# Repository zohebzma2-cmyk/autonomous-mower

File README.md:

# Autonomous Zero-Turn Retrofit Kit

> **Most open-source mowers convert a toy robot-mower. This retrofits a 615 lb commercial gas zero-turn.**

*Parametric CAD, spec-matched to the full published envelope (1968 × 1610 × 1039 mm · deck 1321 mm · tyres 508/279 mm) — [still renders](gallery.html) · [carrier PCB](hardware/pcb/)*

Turn a seated zero-turn mower into a self-driving, iPad-controlled robot — **RTK GPS + LiDAR + cameras + on-device AI** — weatherproofed to live outdoors, and **reproducible on any ZTR** by re-measuring a handful of dimensions.

> **Status: 🔧 in active build.** Design, CAD, firmware, control software, and docs are complete and verified (69/69 tests). The machine is currently being built in person — parts on order, brackets printing, wiring the kill-chain first. This is a multi-month, safety-gated build, documented as it happens — not a plug-and-play kit.

**Confirmed reference machine:** Gravely **ZT X 52** · ~2021 · **Kohler 7000** (24 hp, 725 cc) · electric PTO clutch.

> 🏁 **New here? Start with [`docs/00-BUILD-MANUAL.md`](docs/00-BUILD-MANUAL.md)** — the end-to-end build sequence.
>
> 🕹️ **Already RC-controlled (tracked / slope mower)?** [`docs/ADAPT-RC-MOWER.md`](docs/ADAPT-RC-MOWER.md). The Pixhawk drops in front of the stock drive controller, so you skip the actuators and ESP32.
>
> 🚜 **Phase 3 — the whole rig:** [`docs/ATTACHMENTS.md`](docs/ATTACHMENTS.md) — self-dumping power bagger, rotating blower/trimmer boom, FIMCO tow sprayer with speed-proportional dosing, TPMS, self-start ignition + choke, and the no-rut 3-point turn planner (physics inside).
>
> 📓 **How it evolved:** [`docs/DESIGN-LOG.md`](docs/DESIGN-LOG.md) — every iteration, every wrong turn, constraints A–Z.
> **What's next:** [`docs/ROADMAP-75.md`](docs/ROADMAP-75.md) — 75 planned upgrades.
> **Ordering:** [`cart/ORDER.md`](cart/ORDER.md) + machine-readable [`cart/ORDER-SHEET.csv`](cart/ORDER-SHEET.csv).
> **Building:** [`docs/MEASURE.md`](docs/MEASURE.md) (the 10-minute caliper session — do this first) · [`docs/PRINT-QUEUE.md`](docs/PRINT-QUEUE.md) (40 parts, grams + hours) · [`docs/TOOLS.md`](docs/TOOLS.md) · [`docs/SUBSTITUTIONS.md`](docs/SUBSTITUTIONS.md) · [`docs/CHANGELOG.md`](docs/CHANGELOG.md).
>
> 🌐 **Interactive writeup:** [zohebalvi.com/projects/autonomous-mower](https://zohebalvi.com/projects/autonomous-mower.html) — 3D model, live control-UI demo, architecture, and the full parts list with order links.

> ⚠️ **A 52″ mower deck can kill.** Read [`docs/BUILD.md` §0 Safety](docs/BUILD.md) before powering anything. **Blades stay disconnected until drive + navigation + every failsafe is proven.**

---

## The architecture in one line

**ArduPilot Rover** on a Pixhawk 6C owns drive + RTK navigation + the failsafe chain (skid-steer fits a ZTR natively); a **Raspberry Pi 5 + Hailo-8L** (13 TOPS) rides shotgun for LiDAR obstacle-stop and camera AI, talking to the FC over MAVLink; an **ESP32** closes the lap-bar position loop the autopilot can't drive directly. One web UI serves both an iPad over WiFi and an on-unit touchscreen.

```
        ┌───────────── SENSE ─────────────┐   ┌────── THINK ──────┐   ┌──── ACT ────┐
  Dual RTK GPS (±2 cm, ~0.4° heading) ─────┼──► Pixhawk 6C ────────┼──► lap-bar L/R
  360° LiDAR ──────────────┐               │   (ArduPilot Rover)   │   (via ESP32)
  Front + rear cameras ────┼──► Pi 5 + Hailo├── MAVLink ───────────┤
  Overhead ultrasonic ─────┘   (vision/UI) │   ESP32 (lap-bar PID) ├──► PTO relay
                                           └───────────────────────┘   (blades)
```

---

## The machine — down to the millimetre

| | Gravely ZT X 52 (Kohler 915256) |
|---|---|
| Overall | **1968 × 1610 × 1039 mm** (L×W×H) |
| Curb weight | 615 lb (279 kg) |
| Cutting deck | **1321 mm** (52″), 11-ga fabricated |
| Rear drive wheels | 20×10-8 → **Ø 508 mm**, 254 mm wide |
| Front casters | 11×6-5 → **Ø 279 mm** |
| Seat pan height | 580 mm off ground (**no factory ROPS**) |
| Frame rail | 50.8 mm square tube |
| Lap-bar tube | **Ø 25.4 mm** round steel (MIC to confirm), 560 mm spacing, ~90 mm throw |
| Powertrain | 24 hp Kohler 7000 (725 cc) · Hydro-Gear ZT-2200 · 7 mph · **electric PTO** |

Retrofit parts are modeled to their datasheets — e.g. the **PA-14P actuator** (retracted 241.6 mm, Ø38.1 mm body, 6.35 mm clevis pin), **simpleRTK2B** (68.58 × 53.34 mm, Arduino-Uno footprint), **RPLidar A1M8** (teardrop 96.74 × 70.28 mm base). See [`cad/params.scad`](cad/params.scad).

---

## What's in the repo

```
autonomous-mower/
├── docs/
│   ├── 00-BUILD-MANUAL.md   ← START HERE — Phase 0–6 build sequence
│   ├── BUILD.md             ← full build & SAFETY spec (architecture, training, go/no-go)
│   ├── WIRING.md            ← power distribution, kill-chain, per-module pinouts
│   ├── PRINT_GUIDE.md       ← per-part orientation, brim, supports, plate batching
│   └── wiring-diagram.svg
├── cad/                     ← parametric OpenSCAD — 40 print-ready parts
│   ├── params.scad          ← ★ MASTER PARAMETERS — edit SECTION 1 to fit any ZTR
│   ├── assembly.scad        ← whole machine; SHOW=all|body|black|retro for multi-material export
│   ├── mower.scad           ← parametric mower mock (context)
│   ├── {enclosure,actuator_brackets,gps_mast,lidar_mount,camera_mount,controls_bracket,badge,attachments_brackets,sensor_mounts}.scad
│   ├── export_stl.sh        ← export every PRINT_* part + bed-fit gate (rejects > 145 mm)
│   ├── bake_brims.sh        ← welds a bed-adhesion brim onto every part
│   ├── render_gallery.sh · render_hero.py ← gallery stills · README orbit GIF + social card
│   └── stl/ · renders/ · vendor/
├── software/
│   ├── companion/           ← Python: app.py (HTTP+SSE), safety.py, vision.py, missions.py, mav.py
│   ├── ui/                  ← the control UI (iPad + on-unit kiosk)
│   ├── tests/               ← 69 stdlib tests (safety, geofence, attachments, turns, coverage, keep-outs, vision, mission encoding)
│   └── deploy/              ← systemd service + Chromium kiosk autostart
├── firmware/
│   ├── lapbar_controller/   ← ESP32: FC-PWM → pot → BTS7960 position loop, fail-to-neutral
│   └── ardupilot/           ← rover_params.parm (skid-steer, RTK, geofence, moving-baseline)
├── hardware/pcb/            ← ★ MowerCarrier: power + kill-chain + ESP32 carrier board
│   └── kicad/               ← generated KiCad 9 project (ERC/DRC clean) + Gerbers — read REVIEW.md before fab
│   ├── schematic.svg · layout.svg · render-*.png   ← exported from the KiCad project
│   └── README.md · netlist.md · BOM.md · FABRICATION.md
└── cart/                    ← ORDER.md (real BOM + links), order.html
```

---

## Quickstart

### CAD → STL
```bash
cd cad
# 1. Edit params.scad SECTION 1 to your machine — start from a profile in cad/profiles/
#    (zt-x-52.scad = the reference build; generic-60in.scad = commercial-class starting point)
#    or generate your block interactively: zohebalvi.com/mower → "Adapt it to YOUR mower"
openscad assembly.scad          # see the whole machine
./export_stl.sh                 # export all printable parts + bed-fit check
./bake_brims.sh                 # weld brims for adhesion
./render_gallery.sh             # machine stills; python3 render_hero.py re-shoots the orbit GIF (needs Pillow)
# slice cad/stl/brim/*.stl in FlashPrint for the Adventurer 3 (ASA or PETG)
```

### Dev setup (once — user-level, no sudo/Homebrew)
```bash
./scripts/setup-dev.sh            # uv + Python 3.12 .venv + OpenSCAD (+ --kicad: KiCad, Freerouting, arduino-cli)
./scripts/check.sh --full --sitl  # every gate: tests, mypy, CAD asserts, renders, docs, SITL end-to-end
```

### Control software (runs today, no hardware)
```bash
python3 software/companion/app.py --sim --port 8080
# open http://localhost:8080 — arm, draw a zone, run a coverage mission in simulation
python3 software/tests/test_backend.py       # 69/69
./scripts/sitl.sh                 # the REAL ArduPilot Rover 4.7.1 firmware (SITL) behind the same UI
```

### Firmware
- **ESP32:** flash `firmware/lapbar_controller/lapbar_controller.ino` (Arduino IDE / arduino-cli).
- **ArduPilot:** load `firmware/ardupilot/rover_params.parm` in Mission Planner (skid-steer + RTK + failsafes; moving-baseline block commented for the dual-antenna heading upgrade).

---

## Training — all three, built in order

1. **Teach-and-repeat** — drive the path once, it repeats the RTK track.
2. **Boundary → auto-coverage** — drive the perimeter, the planner fills it with rows and uploads them as an ArduPilot AUTO mission. It handles real yards: L/U shapes (cell decomposition, routed transits), rows along the direction with the fewest turns, **keep-outs** (beds, trees, the shed — or spots the sonar keeps hitting), no-rut turns with **perimeter laps** for the headland, and shows m², minutes and % covered before it moves.

3. **AI learns the yard** — the camera/LiDAR model refines a semantic map over runs (Hailo).

---

## Precision

The upgrade that matters is **dual-antenna moving-baseline heading**. One RTK antenna gives a great position but a noisy heading at a standstill; a second antenna on a ≥ 500 mm baseline fixes heading geometrically (~0.4°), turning ~10 cm cross-track into a few cm. Config in `firmware/ardupilot/rover_params.parm`.

| | |
|---|---|
| Position | **±2 cm** RTK-fixed (u-blox ZED-F9P) |
| Heading | **~0.4°** moving-baseline (dual antenna) |
| Cross-track | few cm, row to row |
| On-device AI | **13 TOPS** (Hailo-8L), INT8, < 30 ms target, no cloud (model training is hardware-gated) |

---

## Safety — a layered kill chain (wire & test this FIRST)

No single failure leaves the machine moving. Blades stay disconnected until every layer is proven.

1. **Physical e-stop** (normally-closed) — in series with the drive relay + PTO relay; cuts power independent of any code.
2. **RC kill** — an independent FlySky channel → ArduPilot RC failsafe → HOLD + disarm.
3. **Software interlock** (`safety.py`) — evaluates incline (15° cutoff), overhead (1.6 m), and obstacle every cycle; priority `e-stop > slope > overhead > obstacle`.
4. **Fail-to-neutral** — on e-stop or signal loss the ESP32 drives the lap bars to center, then coasts; ArduPilot failsafes (GPS loss, geofence, low battery) hold.

Full pinout + kill-chain wiring in [`docs/WIRING.md`](docs/WIRING.md).

---

## Bill of materials

Real, in-stock parts — verified against live listings, no fabricated SKUs. Two tiers: **functional ≈ $1,644**, or **precision ≈ $1,812** with the dual-antenna heading kit. Full itemized sheet with links in [`cart/ORDER.md`](cart/ORDER.md).

- **Navigation / compute:** Pixhawk 6C ([Holybro](https://holybro.com/products/pixhawk-6c)) · simpleRTK2B + ANN-MB-00 ([ArduSimple](https://www.ardusimple.com/product/simplertk2b/)) · Pi 5 + Hailo AI HAT+ ([PiShop](https://www.pishop.us/product/raspberry-pi-ai-hat-13-tops/))
- **Perception:** RPLidar A1M8 · 2× Pi Camera 3 · JSN-SR04T ultrasonic
- **Steering / drive:** 2× Progressive Automations PA-14P · 2× BTS7960 · ESP32
- **Safety / power:** IP65 NC e-stop · 40 A relays · PM02 power module · fuse block · bucks

---

## Adapting to another zero-turn

Open [`cad/params.scad`](cad/params.scad) → **SECTION 1**, re-measure the lap bars / frame / seat, re-render, re-slice. That's the whole port — the mounts, brackets, and masts regenerate around your numbers. Toro, Bad Boy, Spartan, Ferris, Scag, etc.

---

## Status & honest limitations

Design + CAD + firmware + control software + docs are complete and verified (69/69 tests). The build is **in progress in person**. Remaining work is hardware-gated: SITL/on-FC validation of the MAVLink handshake, training the Hailo `.hef` model, and the future fleet/RaaS layer. See [`docs/BUILD.md §12`](docs/BUILD.md).

## Related open-source mowers & rovers

This project stands on the shoulders of a great open community — go star these too:

- **[OpenMower](https://github.com/ClemensElflein/OpenMower)** (Clemens Elflein) — the flagship: retrofits *consumer* robot mowers with a custom mainboard + RTK + ROS. Same RTK/Pi/vision philosophy; we take it to a full-size gas ZTR.
- **[Ardumower / Sunray](https://github.com/Ardumower/Sunray)** — the original DIY-mower ecosystem; Sunray pioneered RTK-without-a-perimeter-wire.
- **[ArduPilot Rover](https://ardupilot.org/rover)** — the autopilot this build runs. The [robot-mower threads](https://discuss.ardupilot.org/t/robot-mower-based-on-ardurover/61999) on their Discourse are the best place to talk shop.
- **[Twisted Fields — Acorn](https://github.com/Twisted-Fields/acorn-precision-farming-rover)** & **[FarmBot](https://github.com/farmbot)** — adjacent open outdoor-autonomy / ag-robotics done well.

## Community & contributing

- 💬 **[GitHub Discussions](https://github.com/zohebzma2-cmyk/autonomous-mower/discussions)** — *Show & Tell* your ZTR build, ask in *Q&A*, propose *Ideas*, follow *Build logs*.
- 🔧 **Adapting to a different zero-turn?** That's the whole point — a new machine profile is the most valuable contribution you can make. See [`Adapting to another zero-turn`](#adapting-to-another-zero-turn) and open a PR with your `params.scad` SECTION 1.
- 🛠️ **Custom carrier PCB** — the power/kill-chain/ESP32 board lives in [`hardware/pcb/`](hardware/pcb/): a routed, ERC/DRC-clean KiCad 9 project generated from one Python file, with Gerbers ready for review ([`REVIEW.md`](hardware/pcb/kicad/REVIEW.md) first). Remix it for your machine.
- See [`CONTRIBUTING.md`](CONTRIBUTING.md) for the safety-gated workflow. Good first issues are labeled `good first issue`.

## License & safety

Open source under the [MIT License](LICENSE). ⚠️ **This drives a machine with large blades that can kill** — it's released for education/research; you are solely responsible for safe construction, testing, supervision, and local-law compliance. Keep blades disconnected until every failsafe is proven.

*A personal robotics project by [Zoheb Alvi](https://zohebalvi.com).*

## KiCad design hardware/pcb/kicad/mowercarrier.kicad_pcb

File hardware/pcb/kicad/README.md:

# MowerCarrier Rev A.1 — KiCad 9 project (generated)

Power input + reverse-polarity protection + 30 A main fuse + five fused branches, the
hardware kill chain (E-stop NC contacts in series with FET-switched relay coils), and the
ESP32-DevKitC carrier for the lap-bar controller. 120 × 100 mm, 2 layers, 2 oz copper.

**The `.kicad_*` files are generated. Edit `design.py` (parts + nets) or `gen_pcb.py`
(placement, pours, routing), then regenerate** — don't hand-edit the outputs, they'd be
overwritten.

```bash
./scripts/setup-dev.sh --kicad          # once: KiCad 9, Java 25 JRE, Freerouting 1.9.0, arduino-cli
hardware/pcb/kicad/gen_kicad.sh         # schematic -> placement -> pours -> autoroute -> GND pour
./scripts/check.sh                      # runs ERC + DRC (errors, schematic parity) on the result
```

| File | What |
|---|---|
| `design.py` | single source of truth: every part (symbol, footprint, LCSC/MPN) and every pin's net; the Rev A → A.1 corrections are listed at the top |
| `gen_schematic.py` | writes `mowercarrier.kicad_sch` from KiCad's own library symbols (net labels on every pin, no-connect flags on the rest) |
| `gen_footprints.py` | `MowerCarrier.pretty/` — the Songle SLA relay footprint, from Songle's drilling drawing |
| `gen_pcb.py` | placement table, trunk pours + track keepouts, Q1 heatsink keepout, Freerouting (DRC-verified, retried), fuse-clip + GND pours |
| `gen_kicad.py` | runs it all, then exports `fab/`, `../schematic.svg`, `../layout.svg`, `../render-*.png` |
| `mowercarrier.kicad_dru` | the two scoped DRC exceptions, with the reasons |
| `fab/` | Gerbers + drill (zip for JLCPCB), pick-and-place CSV, grouped BOM with LCSC numbers |
| `REVIEW.md` | **read before ordering** — what's verified, what isn't, and the items a human must sign off |

## Verified (by the tools, on every regeneration)

- **ERC: 0 violations.** The exported KiCad netlist matches `design.py` net for net.
- **DRC: 0 violations of any severity, 0 unconnected, 0 schematic-parity issues.** Two scoped
  exceptions live in `mowercarrier.kicad_dru` (Q1 inside its heatsink; edge-connector silk).
- Footprint pads == symbol pins for every part (asserted by the generator). The route is
  verified with KiCad's DRC inside the generator, which retries with other pass budgets if
  anything is left open.
- **Deterministic:** an unchanged design regenerates byte-identically (`check.sh --full` gates it).

## Not verified by tools — see REVIEW.md

The ESP32 row pitch of *your* DevKit, Q1's insulating kit (required: its heatsink is grounded),
and a human look at the autorouted logic nets.

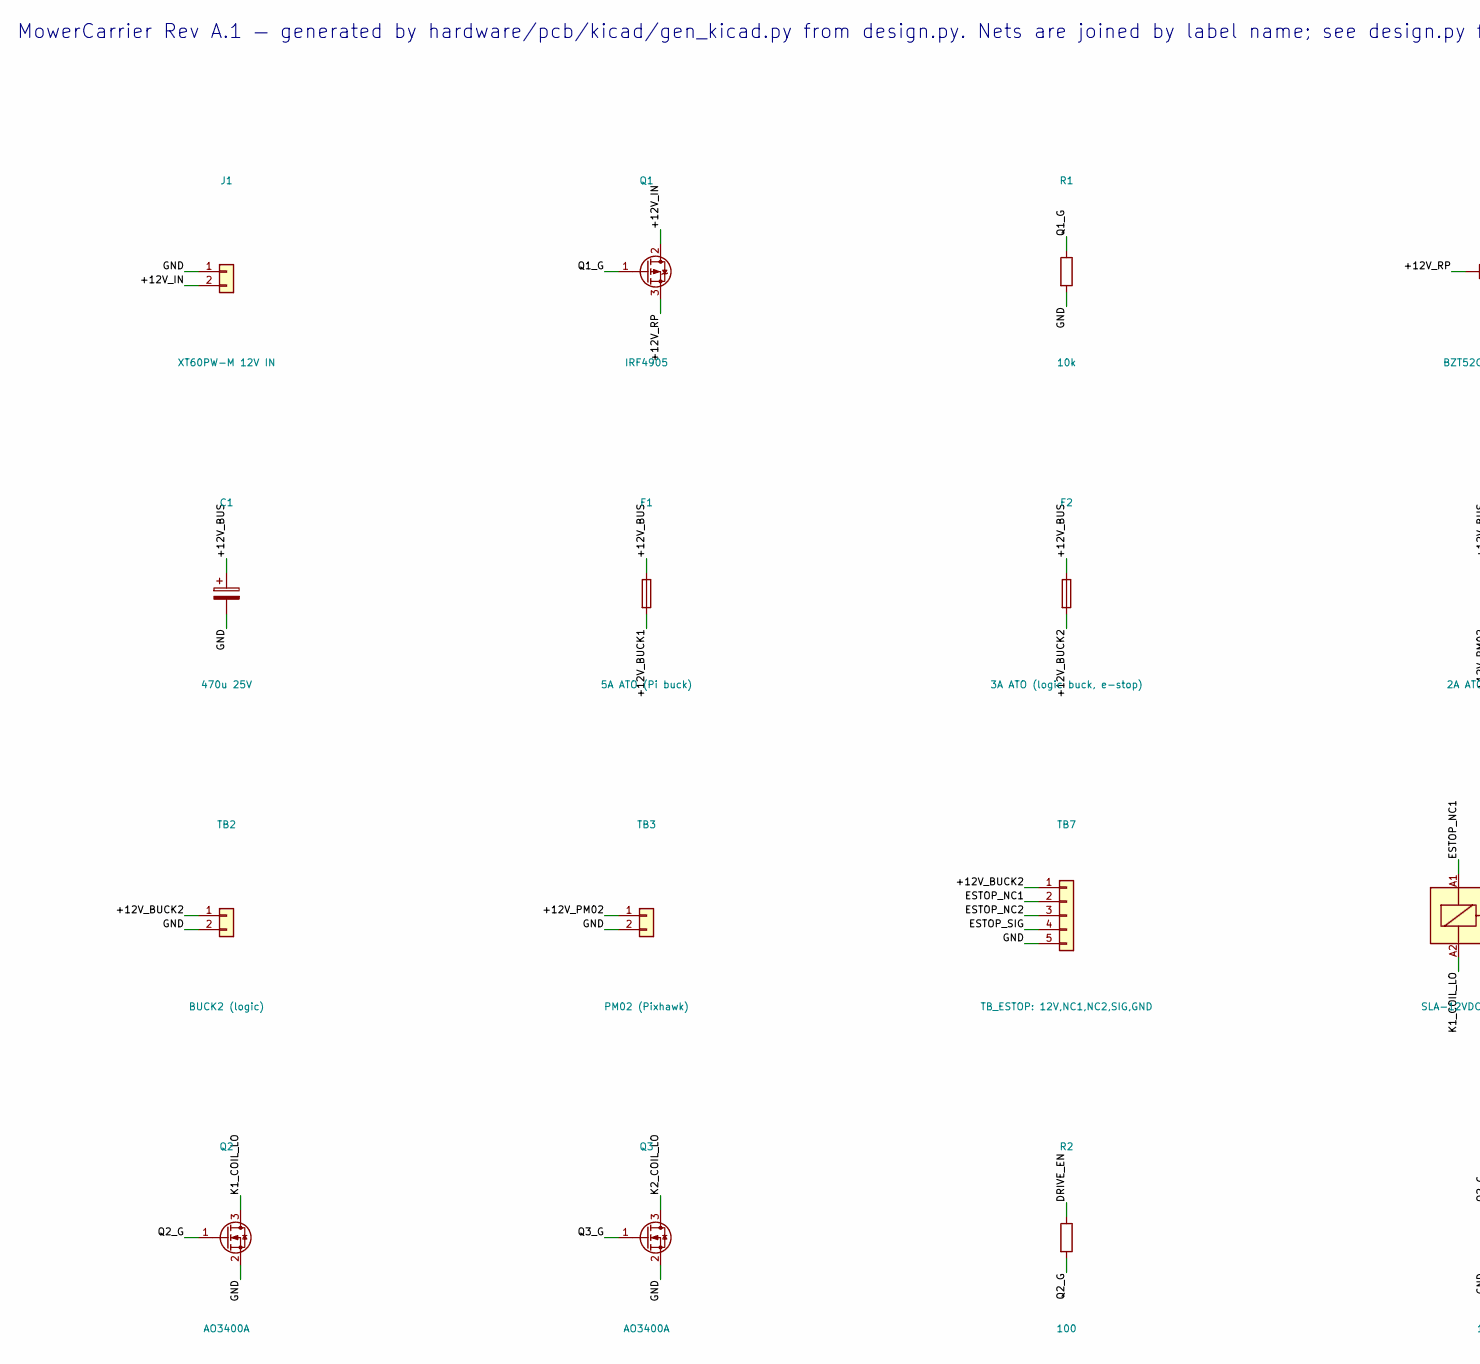
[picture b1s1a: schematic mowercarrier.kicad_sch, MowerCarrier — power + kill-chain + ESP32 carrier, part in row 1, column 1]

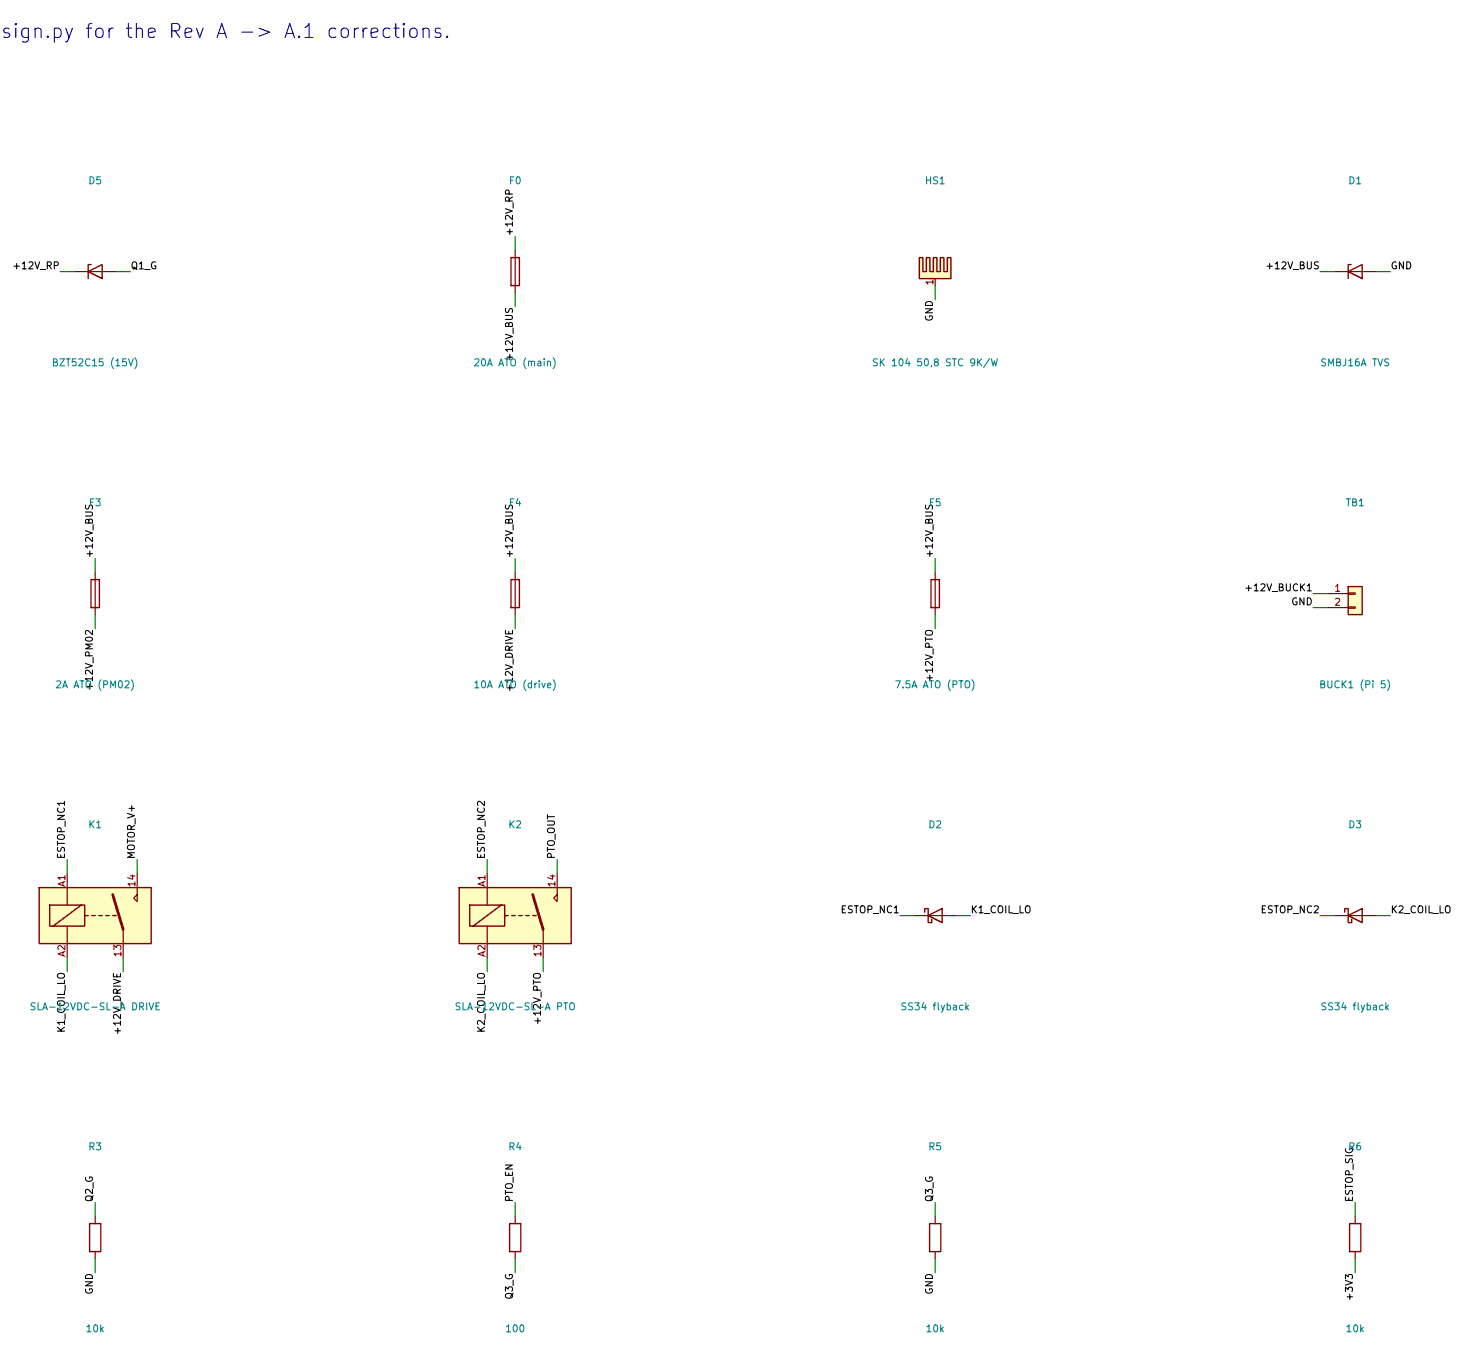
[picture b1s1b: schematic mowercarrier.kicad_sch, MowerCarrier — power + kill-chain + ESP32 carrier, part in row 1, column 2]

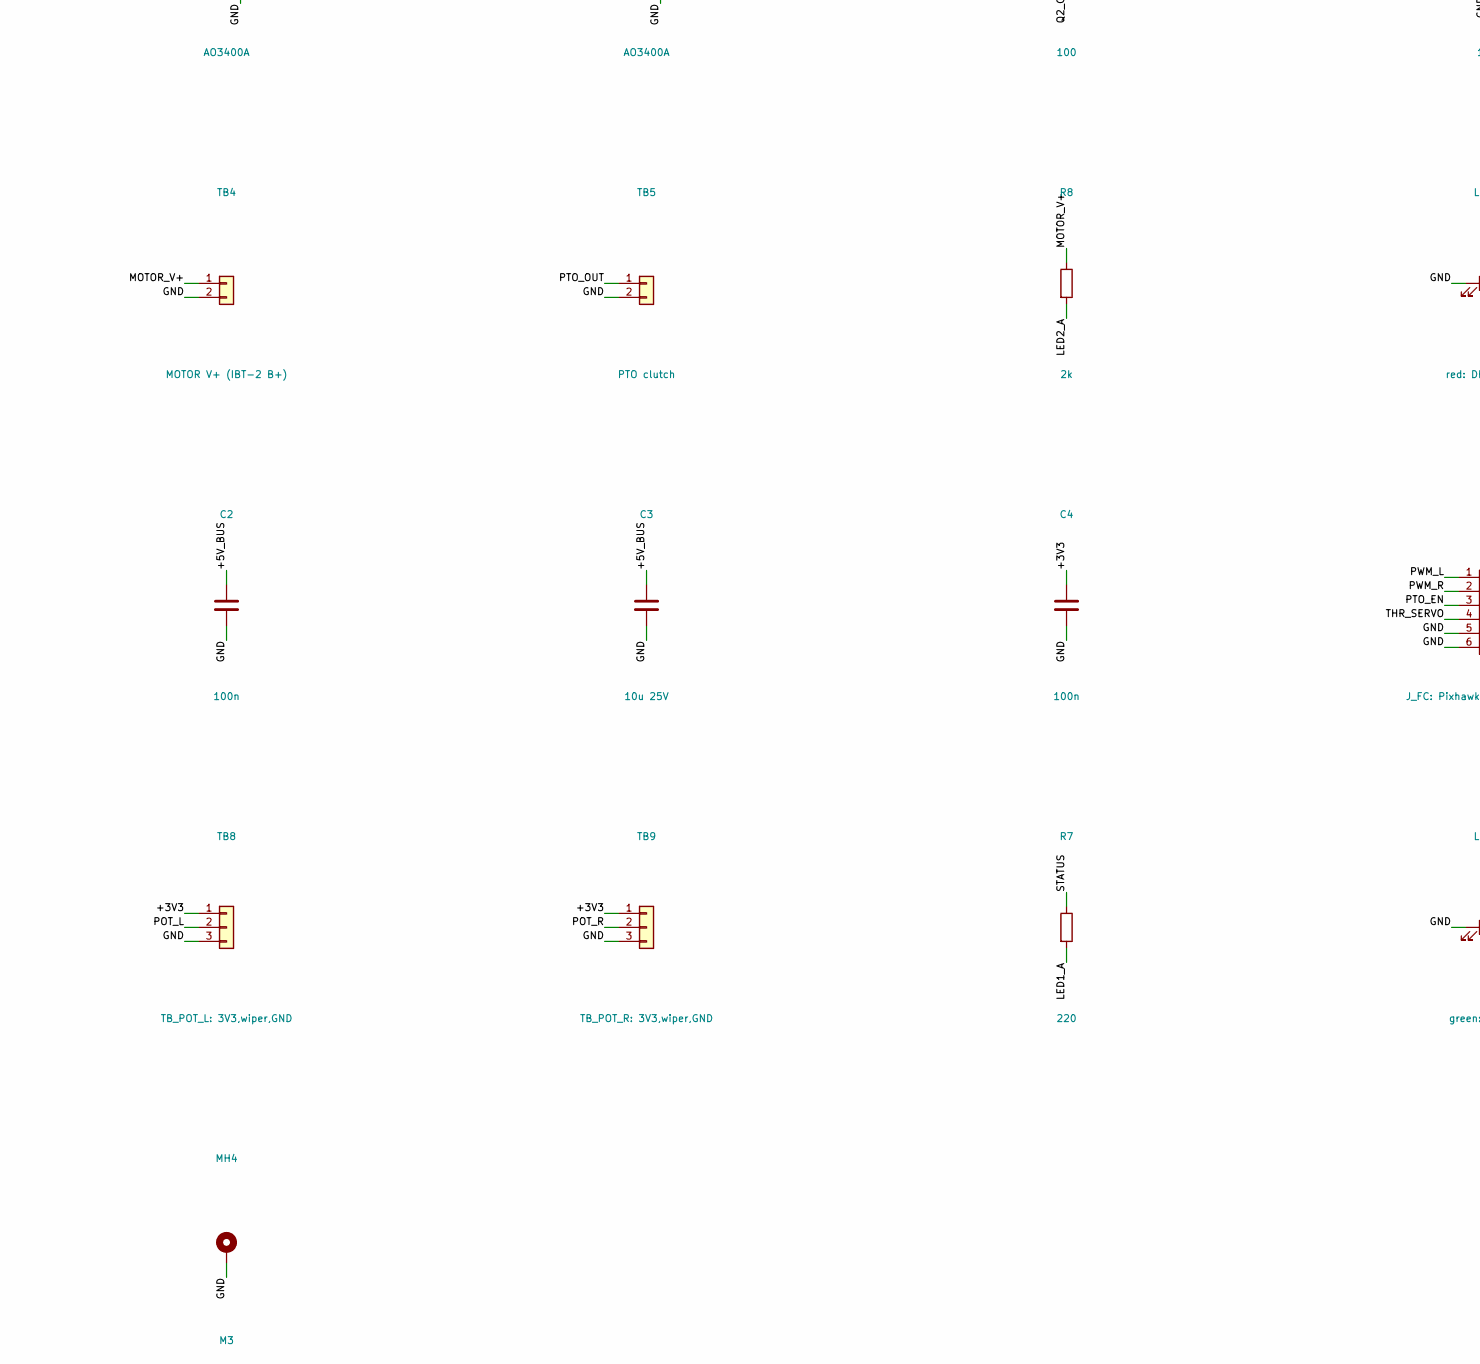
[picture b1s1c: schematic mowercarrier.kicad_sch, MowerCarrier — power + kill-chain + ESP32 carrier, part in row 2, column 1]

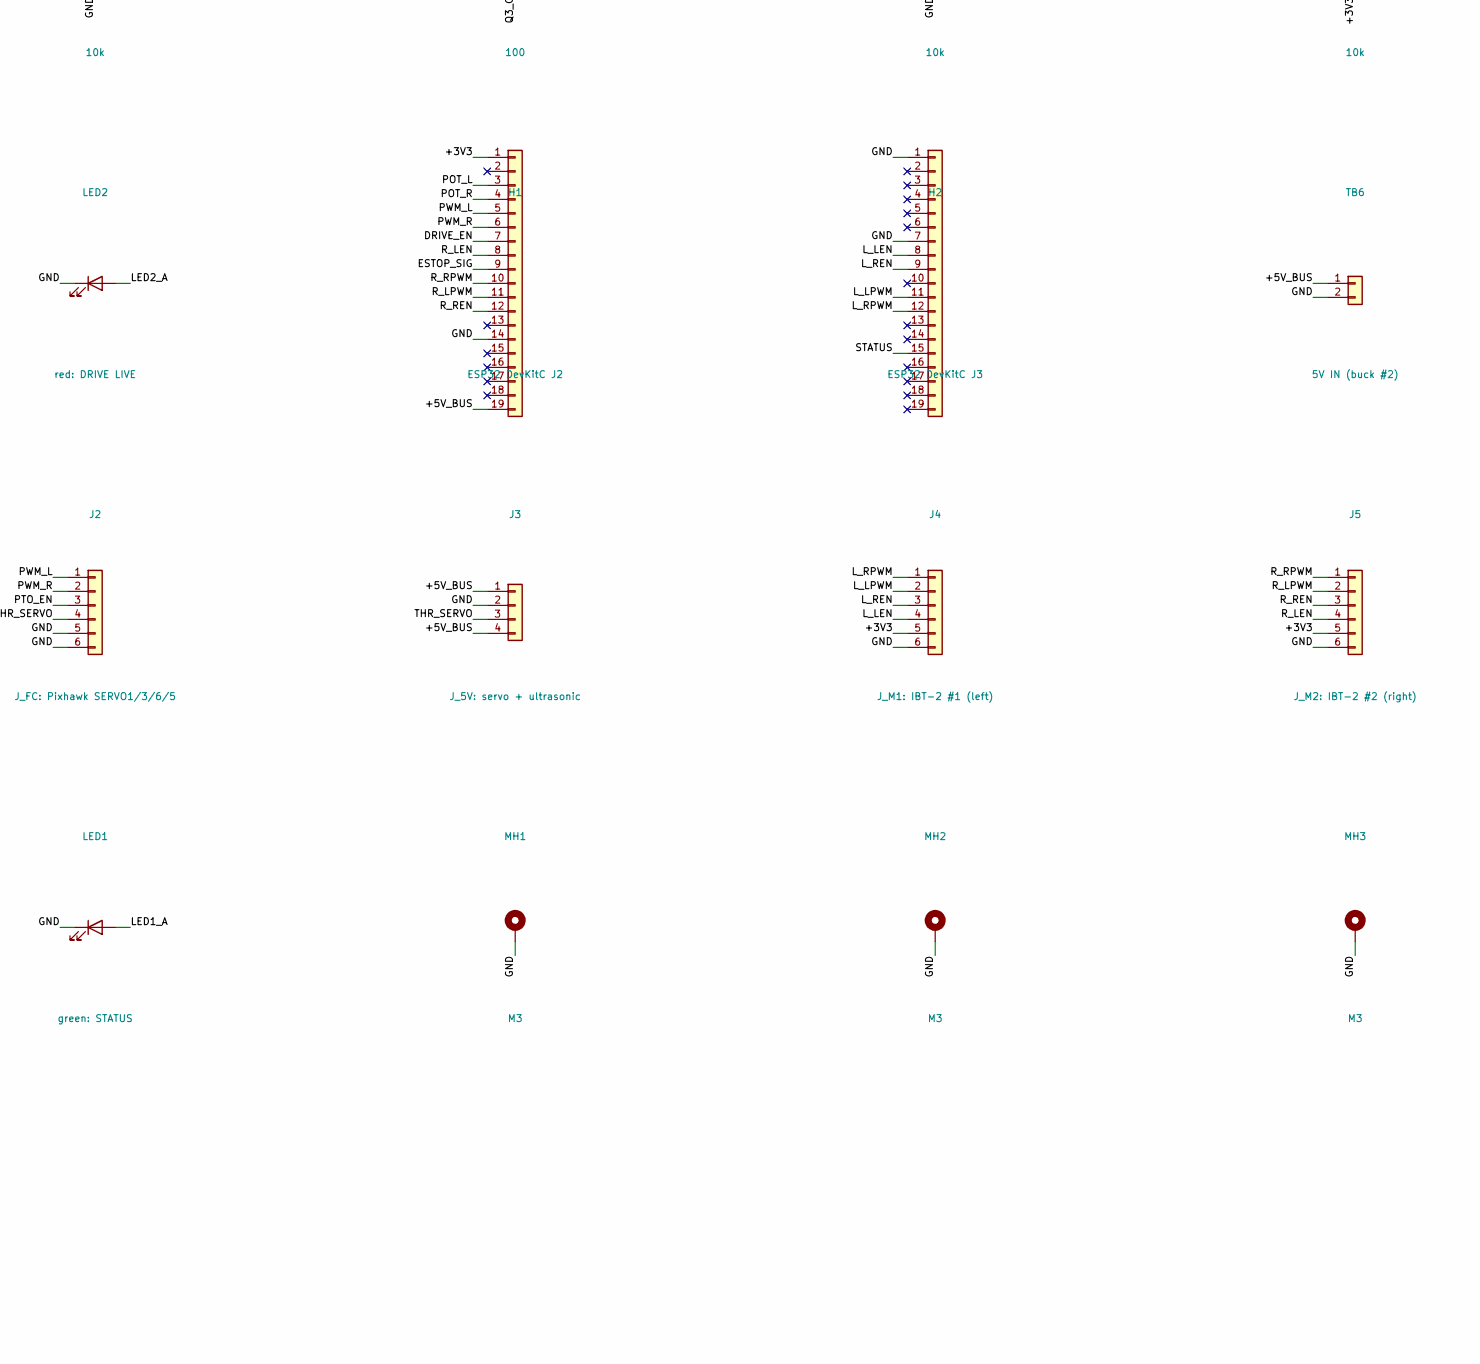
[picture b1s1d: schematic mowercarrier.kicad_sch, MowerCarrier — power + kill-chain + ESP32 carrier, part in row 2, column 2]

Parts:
C1: 470u 25V; CP_Radial_D10.0mm_P5.00mm; LCSC/MPN C43839
C2, C4: 100n; C_0805_2012Metric; LCSC/MPN C49678
C3: 10u 25V; C_0805_2012Metric; LCSC/MPN C15850
D1: SMBJ16A TVS; D_SMB; LCSC/MPN C151254 SMBJ16A
D2, D3: SS34 flyback; D_SMA; LCSC/MPN C8678
D5: BZT52C15 (15V); D_SOD-123; LCSC/MPN BZT52C15 (verify LCSC)
F0: 20A ATO (main); FuseHolder_Blade_ATO_Littelfuse_FLR_178.6165; LCSC/MPN Littelfuse 178.6165.0002 ATO holder (22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
F1: 5A ATO (Pi buck); FuseHolder_Blade_ATO_Littelfuse_FLR_178.6165; LCSC/MPN Littelfuse 178.6165.0002 ATO holder (22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
F2: 3A ATO (logic buck, e-stop); FuseHolder_Blade_ATO_Littelfuse_FLR_178.6165; LCSC/MPN Littelfuse 178.6165.0002 ATO holder (22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
F3: 2A ATO (PM02); FuseHolder_Blade_ATO_Littelfuse_FLR_178.6165; LCSC/MPN Littelfuse 178.6165.0002 ATO holder (22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
F4: 10A ATO (drive); FuseHolder_Blade_ATO_Littelfuse_FLR_178.6165; LCSC/MPN Littelfuse 178.6165.0002 ATO holder (22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
F5: 7.5A ATO (PTO); FuseHolder_Blade_ATO_Littelfuse_FLR_178.6165; LCSC/MPN Littelfuse 178.6165.0002 ATO holder (22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
H1: ESP32 DevKitC J2; PinSocket_1x19_P2.54mm_Vertical; LCSC/MPN C319202
H2: ESP32 DevKitC J3; PinSocket_1x19_P2.54mm_Vertical; LCSC/MPN C319202
HS1: SK 104 50,8 STC 9K/W; Heatsink_Fischer_SK104-STC-STIC_35x13mm_2xDrill2.5mm; LCSC/MPN Fischer SK 104 50,8 STC + TO-220 insula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
J1: XT60PW-M 12V IN; AMASS_XT60PW-M_1x02_P7.20mm_Horizontal; LCSC/MPN C98732 XT60PW-M
J2: J_FC: Pixhawk SERVO1/3/6/5; PinHeader_1x06_P2.54mm_Vertical; LCSC/MPN C2337
J3: J_5V: servo + ultrasonic; PinHeader_1x04_P2.54mm_Vertical; LCSC/MPN C2337
J4: J_M1: IBT-2 #1 (left); PinHeader_1x06_P2.54mm_Vertical; LCSC/MPN C2337
J5: J_M2: IBT-2 #2 (right); PinHeader_1x06_P2.54mm_Vertical; LCSC/MPN C2337
K1: SLA-12VDC-SL-A DRIVE; Relay_SPST_Songle_SLA-xxVDC-SL-A; LCSC/MPN SLA-12VDC-SL-A (verify LCSC)
K2: SLA-12VDC-SL-A PTO; Relay_SPST_Songle_SLA-xxVDC-SL-A; LCSC/MPN SLA-12VDC-SL-A (verify LCSC)
LED1: green: STATUS; LED_0805_2012Metric; LCSC/MPN C2297
LED2: red: DRIVE LIVE; LED_0805_2012Metric; LCSC/MPN C84256
MH1, MH2, MH3, MH4: M3; MountingHole_3.2mm_M3_Pad
Q1: IRF4905; TO-220-3_Vertical; LCSC/MPN C2564 IRF4905
Q2, Q3: AO3400A; SOT-23; LCSC/MPN C20917
R1, R3, R5, R6: 10k; R_0805_2012Metric; LCSC/MPN C17414
R2, R4: 100; R_0805_2012Metric; LCSC/MPN C17408
R7: 220; R_0805_2012Metric; LCSC/MPN C17557
R8: 2k; R_0805_2012Metric; LCSC/MPN C17604
TB1: BUCK1 (Pi 5); TerminalBlock_Phoenix_MKDS-1,5-2-5.08_1x02_P5.08mm_Horizont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; LCSC/MPN C474952
TB2: BUCK2 (logic); TerminalBlock_Phoenix_MKDS-1,5-2-5.08_1x02_P5.08mm_Horizont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; LCSC/MPN C474952
TB3: PM02 (Pixhawk); TerminalBlock_Phoenix_MKDS-1,5-2-5.08_1x02_P5.08mm_Horizont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; LCSC/MPN C474952
TB4: MOTOR V+ (IBT-2 B+); TerminalBlock_Phoenix_MKDS-1,5-2-5.08_1x02_P5.08mm_Horizont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; LCSC/MPN C474952
TB5: PTO clutch; TerminalBlock_Phoenix_MKDS-1,5-2-5.08_1x02_P5.08mm_Horizont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; LCSC/MPN C474952
TB6: 5V IN (buck #2); TerminalBlock_Phoenix_MKDS-1,5-2-5.08_1x02_P5.08mm_Horizont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; LCSC/MPN C474952
TB7: TB_ESTOP: 12V,NC1,NC2,SIG,GND; TerminalBlock_Phoenix_MKDS-1,5-5-5.08_1x05_P5.08mm_Horizont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; LCSC/MPN KF128-5.08-5P (verify LCSC)
TB8: TB_POT_L: 3V3,wiper,GND; TerminalBlock_Phoenix_PT-1,5-3-3.5-H_1x03_P3.50mm_Horizontal; LCSC/MPN PT-1,5-3-3.5-H
TB9: TB_POT_R: 3V3,wiper,GND; TerminalBlock_Phoenix_PT-1,5-3-3.5-H_1x03_P3.50mm_Horizontal; LCSC/MPN PT-1,5-3-3.5-H

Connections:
/+3V3: C4.1, H1.1, J4.5, J5.5, R6.2, TB8.1, TB9.1
/+5V_BUS: C2.1, C3.1, H1.19, J3.1, J3.4, TB6.1
/+12V_BUCK1: F1.2, TB1.1
/+12V_BUCK2: F2.2, TB2.1, TB7.1
/+12V_BUS: C1.1, D1.1 (K), F0.2, F1.1, F2.1, F3.1, F4.1, F5.1
/+12V_DRIVE: F4.2, K1.13
/+12V_IN: J1.2, Q1.2 (D)
/+12V_PM02: F3.2, TB3.1
/+12V_PTO: F5.2, K2.13
/+12V_RP: D5.1 (K), F0.1, Q1.3 (S)
/DRIVE_EN: H1.7, R2.1
/ESTOP_NC1: D2.1 (K), K1.A1, TB7.2
/ESTOP_NC2: D3.1 (K), K2.A1, TB7.3
/ESTOP_SIG: H1.9, R6.1, TB7.4
/GND: C1.2, C2.2, C3.2, C4.2, D1.2 (A), H1.14, H2.1, H2.7, HS1.1, J1.1, J2.5, J2.6, J3.2, J4.6, J5.6, LED1.1 (K), LED2.1 (K), MH1.1, MH2.1, MH3.1, MH4.1, Q2.2 (S), Q3.2 (S), R1.2, R3.2, R5.2, TB1.2, TB2.2, TB3.2, TB4.2, TB5.2, TB6.2, TB7.5, TB8.3, TB9.3
/K1_COIL_LO: D2.2 (A), K1.A2, Q2.3 (D)
/K2_COIL_LO: D3.2 (A), K2.A2, Q3.3 (D)
/LED1_A: LED1.2 (A), R7.2
/LED2_A: LED2.2 (A), R8.2
/L_LEN: H2.8, J4.4
/L_LPWM: H2.11, J4.2
/L_REN: H2.9, J4.3
/L_RPWM: H2.12, J4.1
/MOTOR_V+: K1.14, R8.1, TB4.1
/POT_L: H1.3, TB8.2
/POT_R: H1.4, TB9.2
/PTO_EN: J2.3, R4.1
/PTO_OUT: K2.14, TB5.1
/PWM_L: H1.5, J2.1
/PWM_R: H1.6, J2.2
/Q1_G: D5.2 (A), Q1.1 (G), R1.1
/Q2_G: Q2.1 (G), R2.2, R3.1
/Q3_G: Q3.1 (G), R4.2, R5.1
/R_LEN: H1.8, J5.4
/R_LPWM: H1.11, J5.2
/R_REN: H1.12, J5.3
/R_RPWM: H1.10, J5.1
/STATUS: H2.15, R7.1
/THR_SERVO: J2.4, J3.3

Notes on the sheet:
MowerCarrier Rev A.1 — generated by hardware/pcb/kicad/gen_kicad.py from design.py. Nets are joined by label name; see design.py for the Rev A -> A.1 corrections.

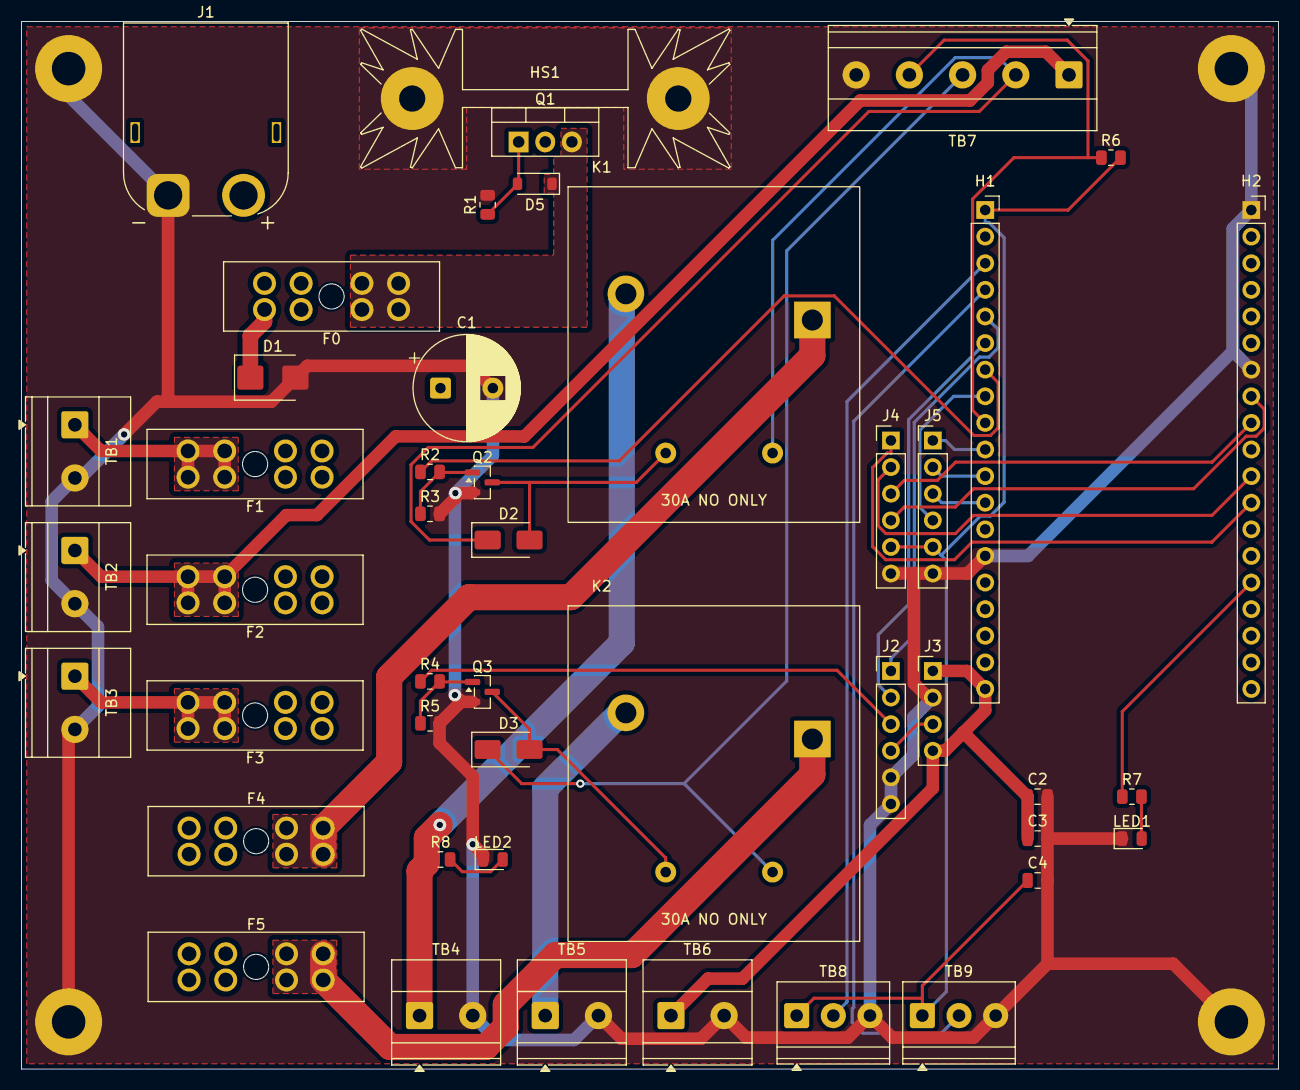
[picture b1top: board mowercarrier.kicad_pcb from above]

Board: 2 copper layers, 120.0 x 100.0 mm, 50 parts (0 on the bottom side), 39 nets.

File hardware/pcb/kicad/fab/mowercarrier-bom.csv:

"Designator","Value","Footprint","LCSC/MPN","Qty"
"C1","470u 25V","Capacitor_THT:CP_Radial_D10.0mm_P5.00mm","C43839","1"
"C2,C4","100n","Capacitor_SMD:C_0805_2012Metric","C49678","2"
"C3","10u 25V","Capacitor_SMD:C_0805_2012Metric","C15850","1"
"D1","SMBJ16A TVS","Diode_SMD:D_SMB","C151254 SMBJ16A","1"
"D2,D3","SS34 flyback","Diode_SMD:D_SMA","C8678","2"
"D5","BZT52C15 (15V)","Diode_SMD:D_SOD-123","BZT52C15 (verify LCSC)","1"
"F0","20A ATO (main)","Fuse:FuseHolder_Blade_ATO_Littelfuse_FLR_178.6165","Littelfuse 178.6165.0002 ATO holder (22.5 A cont.)","1"
"F1","5A ATO (Pi buck)","Fuse:FuseHolder_Blade_ATO_Littelfuse_FLR_178.6165","Littelfuse 178.6165.0002 ATO holder (22.5 A cont.)","1"
"F2","3A ATO (logic buck, e-stop)","Fuse:FuseHolder_Blade_ATO_Littelfuse_FLR_178.6165","Littelfuse 178.6165.0002 ATO holder (22.5 A cont.)","1"
"F3","2A ATO (PM02)","Fuse:FuseHolder_Blade_ATO_Littelfuse_FLR_178.6165","Littelfuse 178.6165.0002 ATO holder (22.5 A cont.)","1"
"F4","10A ATO (drive)","Fuse:FuseHolder_Blade_ATO_Littelfuse_FLR_178.6165","Littelfuse 178.6165.0002 ATO holder (22.5 A cont.)","1"
"F5","7.5A ATO (PTO)","Fuse:FuseHolder_Blade_ATO_Littelfuse_FLR_178.6165","Littelfuse 178.6165.0002 ATO holder (22.5 A cont.)","1"
"H1","ESP32 DevKitC J2","Connector_PinSocket_2.54mm:PinSocket_1x19_P2.54mm_Vertical","C319202","1"
"H2","ESP32 DevKitC J3","Connector_PinSocket_2.54mm:PinSocket_1x19_P2.54mm_Vertical","C319202","1"
"HS1","SK 104 50,8 STC 9K/W","Heatsink:Heatsink_Fischer_SK104-STC-STIC_35x13mm_2xDrill2.5mm","Fischer SK 104 50,8 STC + TO-220 insulating pad","1"
"J1","XT60PW-M 12V IN","Connector_AMASS:AMASS_XT60PW-M_1x02_P7.20mm_Horizontal","C98732 XT60PW-M","1"
"J2","J_FC: Pixhawk SERVO1/3/6/5","Connector_PinHeader_2.54mm:PinHeader_1x06_P2.54mm_Vertical","C2337","1"
"J3","J_5V: servo + ultrasonic","Connector_PinHeader_2.54mm:PinHeader_1x04_P2.54mm_Vertical","C2337","1"
"J4","J_M1: IBT-2 #1 (left)","Connector_PinHeader_2.54mm:PinHeader_1x06_P2.54mm_Vertical","C2337","1"
"J5","J_M2: IBT-2 #2 (right)","Connector_PinHeader_2.54mm:PinHeader_1x06_P2.54mm_Vertical","C2337","1"
"K1","SLA-12VDC-SL-A DRIVE","MowerCarrier:Relay_SPST_Songle_SLA-xxVDC-SL-A","SLA-12VDC-SL-A (verify LCSC)","1"
"K2","SLA-12VDC-SL-A PTO","MowerCarrier:Relay_SPST_Songle_SLA-xxVDC-SL-A","SLA-12VDC-SL-A (verify LCSC)","1"
"LED1","green: STATUS","LED_SMD:LED_0805_2012Metric","C2297","1"
"LED2","red: DRIVE LIVE","LED_SMD:LED_0805_2012Metric","C84256","1"
"Q1","IRF4905","Package_TO_SOT_THT:TO-220-3_Vertical","C2564 IRF4905","1"
"Q2,Q3","AO3400A","Package_TO_SOT_SMD:SOT-23","C20917","2"
"R1,R3,R5,R6","10k","Resistor_SMD:R_0805_2012Metric","C17414","4"
"R2,R4","100","Resistor_SMD:R_0805_2012Metric","C17408","2"
"R7","220","Resistor_SMD:R_0805_2012Metric","C17557","1"
"R8","2k","Resistor_SMD:R_0805_2012Metric","C17604","1"
"TB1","BUCK1 (Pi 5)","TerminalBlock_Phoenix:TerminalBlock_Phoenix_MKDS-1,5-2-5.08_1x02_P5.08mm_Horizontal","C474952","1"
"TB2","BUCK2 (logic)","TerminalBlock_Phoenix:TerminalBlock_Phoenix_MKDS-1,5-2-5.08_1x02_P5.08mm_Horizontal","C474952","1"
"TB3","PM02 (Pixhawk)","TerminalBlock_Phoenix:TerminalBlock_Phoenix_MKDS-1,5-2-5.08_1x02_P5.08mm_Horizontal","C474952","1"
"TB4","MOTOR V+ (IBT-2 B+)","TerminalBlock_Phoenix:TerminalBlock_Phoenix_MKDS-1,5-2-5.08_1x02_P5.08mm_Horizontal","C474952","1"
"TB5","PTO clutch","TerminalBlock_Phoenix:TerminalBlock_Phoenix_MKDS-1,5-2-5.08_1x02_P5.08mm_Horizontal","C474952","1"
"TB6","5V IN (buck #2)","TerminalBlock_Phoenix:TerminalBlock_Phoenix_MKDS-1,5-2-5.08_1x02_P5.08mm_Horizontal","C474952","1"
"TB7","TB_ESTOP: 12V,NC1,NC2,SIG,GND","TerminalBlock_Phoenix:TerminalBlock_Phoenix_MKDS-1,5-5-5.08_1x05_P5.08mm_Horizontal","KF128-5.08-5P (verify LCSC)","1"
"TB8","TB_POT_L: 3V3,wiper,GND","TerminalBlock_Phoenix:TerminalBlock_Phoenix_PT-1,5-3-3.5-H_1x03_P3.50mm_Horizontal","PT-1,5-3-3.5-H","1"
"TB9","TB_POT_R: 3V3,wiper,GND","TerminalBlock_Phoenix:TerminalBlock_Phoenix_PT-1,5-3-3.5-H_1x03_P3.50mm_Horizontal","PT-1,5-3-3.5-H","1"

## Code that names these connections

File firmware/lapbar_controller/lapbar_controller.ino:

// SPDX-License-Identifier: MIT
/* =============================================================================
 * LAP-BAR ACTUATOR CONTROLLER  —  ESP32  (autonomous ZT X 52 retrofit)
 *
 * Closes the position loop ArduPilot can't: the Pixhawk outputs a throttle PWM
 * per side (skid-steer); this reads those, reads each actuator's feedback pot,
 * runs a PID, and drives a BTS7960 H-bridge until each lap bar is at position.
 *
 * FAIL-TO-NEUTRAL (safety): if the e-stop opens OR the FC pulse train is lost
 * (> FAILSAFE_MS), both bars are driven to NEUTRAL (center) and the drivers are
 * disabled, so the hydros return to neutral and the machine coasts to a stop.
 *
 * Board: ESP32 DevKit (38-pin).  Drivers: 2x BTS7960 (IBT-2).
 * See docs/WIRING.md for the full harness + pinout.  Tune the *_CAL + PID below.
 * ============================================================================= */
#include <Arduino.h>

// ---- pin map (must match docs/WIRING.md) -----------------------------------
// FC throttle PWM inputs (input-only GPIOs, interrupt-capable)
const int PIN_PWM_L = 34;
const int PIN_PWM_R = 35;
// Actuator feedback pots (ADC1, input-only). Wiper -> these; ends to 3V3 / GND.
const int PIN_POT_L = 36;   // VP
const int PIN_POT_R = 39;   // VN
// E-stop sense: e-stop NC contact between this pin and GND. OK=LOW, tripped=HIGH.
const int PIN_ESTOP = 25;
// BTS7960 #1 (LEFT):  RPWM, LPWM (PWM via LEDC), R_EN, L_EN (digital enable)
const int L_RPWM = 16, L_LPWM = 17, L_REN = 18, L_LEN = 19;
// BTS7960 #2 (RIGHT)
const int R_RPWM = 26, R_LPWM = 27, R_REN = 14, R_LEN = 33;   // was GPIO12: a boot strapping pin (MTDI)
const int PIN_LED = 2;      // onboard status LED
// MowerCarrier Rev A.1: drives Q2's gate -> DRIVE relay K1 coil (in series with e-stop NC1).
// 10k pulldown on the board: K1 (motor V+) stays OFF while the ESP32 boots/resets.
const int PIN_DRIVE_EN = 32;

// ---- tuning ----------------------------------------------------------------
const int   PWM_MIN = 1000, PWM_MID = 1500, PWM_MAX = 2000;  // FC servo PWM (us)
const int   PWM_DEADBAND = 25;          // us around mid = neutral
const int   POT_L_MIN = 200, POT_L_MAX = 3900;   // CAL: pot raw at full-retract/extend
const int   POT_R_MIN = 200, POT_R_MAX = 3900;   // CAL each actuator
const float KP = 6.0, KI = 0.0, KD = 0.4;        // PID (start P-only; add D to damp)
const int   POS_DEADBAND = 30;          // raw counts: stop hunting near target
const int   DUTY_MAX = 230;             // cap H-bridge duty (0-255)
const int   DUTY_MIN = 40;              // overcome stiction
const unsigned long FAILSAFE_MS = 400;  // no FC pulse this long -> neutral

// ---- PWM input capture (ISR) ----------------------------------------------
volatile unsigned long riseL = 0, riseR = 0, pulseL = PWM_MID, pulseR = PWM_MID;
volatile unsigned long lastEdgeL = 0, lastEdgeR = 0;
void IRAM_ATTR isrL() {
  if (digitalRead(PIN_PWM_L)) riseL = micros();
  else { unsigned long w = micros() - riseL; if (w > 700 && w < 2300) { pulseL = w; lastEdgeL = millis(); } }
}
void IRAM_ATTR isrR() {
  if (digitalRead(PIN_PWM_R)) riseR = micros();
  else { unsigned long w = micros() - riseR; if (w > 700 && w < 2300) { pulseR = w; lastEdgeR = millis(); } }
}

// ---- LEDC PWM channels for the 4 BTS7960 PWM pins --------------------------
const int CH_L_R = 0, CH_L_L = 1, CH_R_R = 2, CH_R_L = 3;
const int CH_PIN[4] = {L_RPWM, L_LPWM, R_RPWM, R_LPWM};   // channel -> pin
// ESP32 Arduino core 3.x replaced ledcSetup/ledcAttachPin and writes by PIN; 2.x writes by
// channel. These two shims keep the sketch's channel numbering and build on both.
void pwmAttach(int pin, int ch) {                      // 20 kHz, 8-bit
#if ESP_ARDUINO_VERSION_MAJOR >= 3
  ledcAttachChannel(pin, 20000, 8, ch);
#else
  ledcSetup(ch, 20000, 8); ledcAttachPin(pin, ch);
#endif
}
void pwmWrite(int ch, int duty) {
#if ESP_ARDUINO_VERSION_MAJOR >= 3
  ledcWrite(CH_PIN[ch], duty);
#else
  ledcWrite(ch, duty);
#endif
}
void setupDriver(int rpwm, int lpwm, int ren, int len, int chR, int chL) {
  pinMode(ren, OUTPUT); pinMode(len, OUTPUT);
  digitalWrite(ren, HIGH); digitalWrite(len, HIGH);     // enable both half-bridges
  pwmAttach(rpwm, chR);
  pwmAttach(lpwm, chL);
}
// duty: -255..255  (+ = extend, - = retract)
void drive(int chR, int chL, int duty) {
  duty = constrain(duty, -DUTY_MAX, DUTY_MAX);
  if (duty >= 0) { pwmWrite(chR, duty); pwmWrite(chL, 0); }
  else           { pwmWrite(chR, 0);    pwmWrite(chL, -duty); }
}
void disableAll() { pwmWrite(CH_L_R,0); pwmWrite(CH_L_L,0); pwmWrite(CH_R_R,0); pwmWrite(CH_R_L,0);
  digitalWrite(L_REN,LOW); digitalWrite(L_LEN,LOW); digitalWrite(R_REN,LOW); digitalWrite(R_LEN,LOW); }
void enableAll() { digitalWrite(L_REN,HIGH); digitalWrite(L_LEN,HIGH); digitalWrite(R_REN,HIGH); digitalWrite(R_LEN,HIGH); }

// ---- per-side PID ----------------------------------------------------------
struct PID { float i=0, prev=0; } pidL, pidR;
int step(PID &s, int target, int actual) {
  if (abs(target - actual) < POS_DEADBAND) { s.i = 0; return 0; }
  float e = target - actual;
  s.i = constrain(s.i + e, -2000, 2000);
  float d = e - s.prev; s.prev = e;
  float u = KP*e + KI*s.i + KD*d;
  int duty = (int)(u * 0.06);                 // scale error(counts)->duty
  if (duty != 0 && abs(duty) < DUTY_MIN) duty = (duty>0?DUTY_MIN:-DUTY_MIN);
  return duty;
}

int targetFromPwm(int us, int potMin, int potMax) {
  if (abs(us - PWM_MID) < PWM_DEADBAND) return (potMin + potMax) / 2;   // neutral
  return map(constrain(us, PWM_MIN, PWM_MAX), PWM_MIN, PWM_MAX, potMin, potMax);
}

void setup() {
  Serial.begin(115200);
  pinMode(PIN_PWM_L, INPUT); pinMode(PIN_PWM_R, INPUT);
  pinMode(PIN_DRIVE_EN, OUTPUT); digitalWrite(PIN_DRIVE_EN, LOW);   // motor power off until ready
  pinMode(PIN_ESTOP, INPUT_PULLUP); pinMode(PIN_LED, OUTPUT);
  attachInterrupt(PIN_PWM_L, isrL, CHANGE);
  attachInterrupt(PIN_PWM_R, isrR, CHANGE);
  setupDriver(L_RPWM, L_LPWM, L_REN, L_LEN, CH_L_R, CH_L_L);
  setupDriver(R_RPWM, R_LPWM, R_REN, R_LEN, CH_R_R, CH_R_L);
  Serial.println("lapbar_controller ready");
  // Bridges + PWM capture are configured, so boot-time pin glitches can no longer move the
  // bars: let K1 energise (the e-stop NC contact is still in series with its coil).
}

void loop() {
  unsigned long now = millis();
  bool estop = digitalRead(PIN_ESTOP);                 // HIGH = tripped (NC opened)
  bool lostL = (now - lastEdgeL) > FAILSAFE_MS;
  bool lostR = (now - lastEdgeR) > FAILSAFE_MS;
  bool fail  = estop || lostL || lostR;
  // DRIVE_EN stays HIGH through a software failsafe: fail-to-neutral NEEDS motor power to
  // centre the bars. The e-stop cuts K1 in hardware regardless (and grounds the magneto).
  digitalWrite(PIN_DRIVE_EN, estop ? LOW : HIGH);

  int potL = analogRead(PIN_POT_L), potR = analogRead(PIN_POT_R);
  int tgtL = fail ? (POT_L_MIN+POT_L_MAX)/2 : targetFromPwm(pulseL, POT_L_MIN, POT_L_MAX);
  int tgtR = fail ? (POT_R_MIN+POT_R_MAX)/2 : targetFromPwm(pulseR, POT_R_MIN, POT_R_MAX);

  if (fail) {                                          // FAIL-TO-NEUTRAL
    enableAll();                                       // keep bridges live just long enough
    drive(CH_L_R, CH_L_L, step(pidL, tgtL, potL));     // drive bars to center
    drive(CH_R_R, CH_R_L, step(pidR, tgtR, potR));
    bool centered = abs(tgtL-potL)<POS_DEADBAND && abs(tgtR-potR)<POS_DEADBAND;
    if (centered) disableAll();                        // then cut power (coast to neutral)
    digitalWrite(PIN_LED, (now/120)%2);                // fast blink = failsafe
  } else {
    enableAll();
    drive(CH_L_R, CH_L_L, step(pidL, tgtL, potL));
    drive(CH_R_R, CH_R_L, step(pidR, tgtR, potR));
    digitalWrite(PIN_LED, HIGH);                       // solid = armed/ok
  }

  static unsigned long tlog = 0;
  if (now - tlog > 500) { tlog = now;
    Serial.printf("L pwm%lu pot%d tgt%d | R pwm%lu pot%d tgt%d | %s\n",
      pulseL, potL, tgtL, pulseR, potR, tgtR, fail ? "FAILSAFE" : "run"); }
  delay(10);                                           // ~100 Hz loop
}

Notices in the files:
README.md:
License: MIT
